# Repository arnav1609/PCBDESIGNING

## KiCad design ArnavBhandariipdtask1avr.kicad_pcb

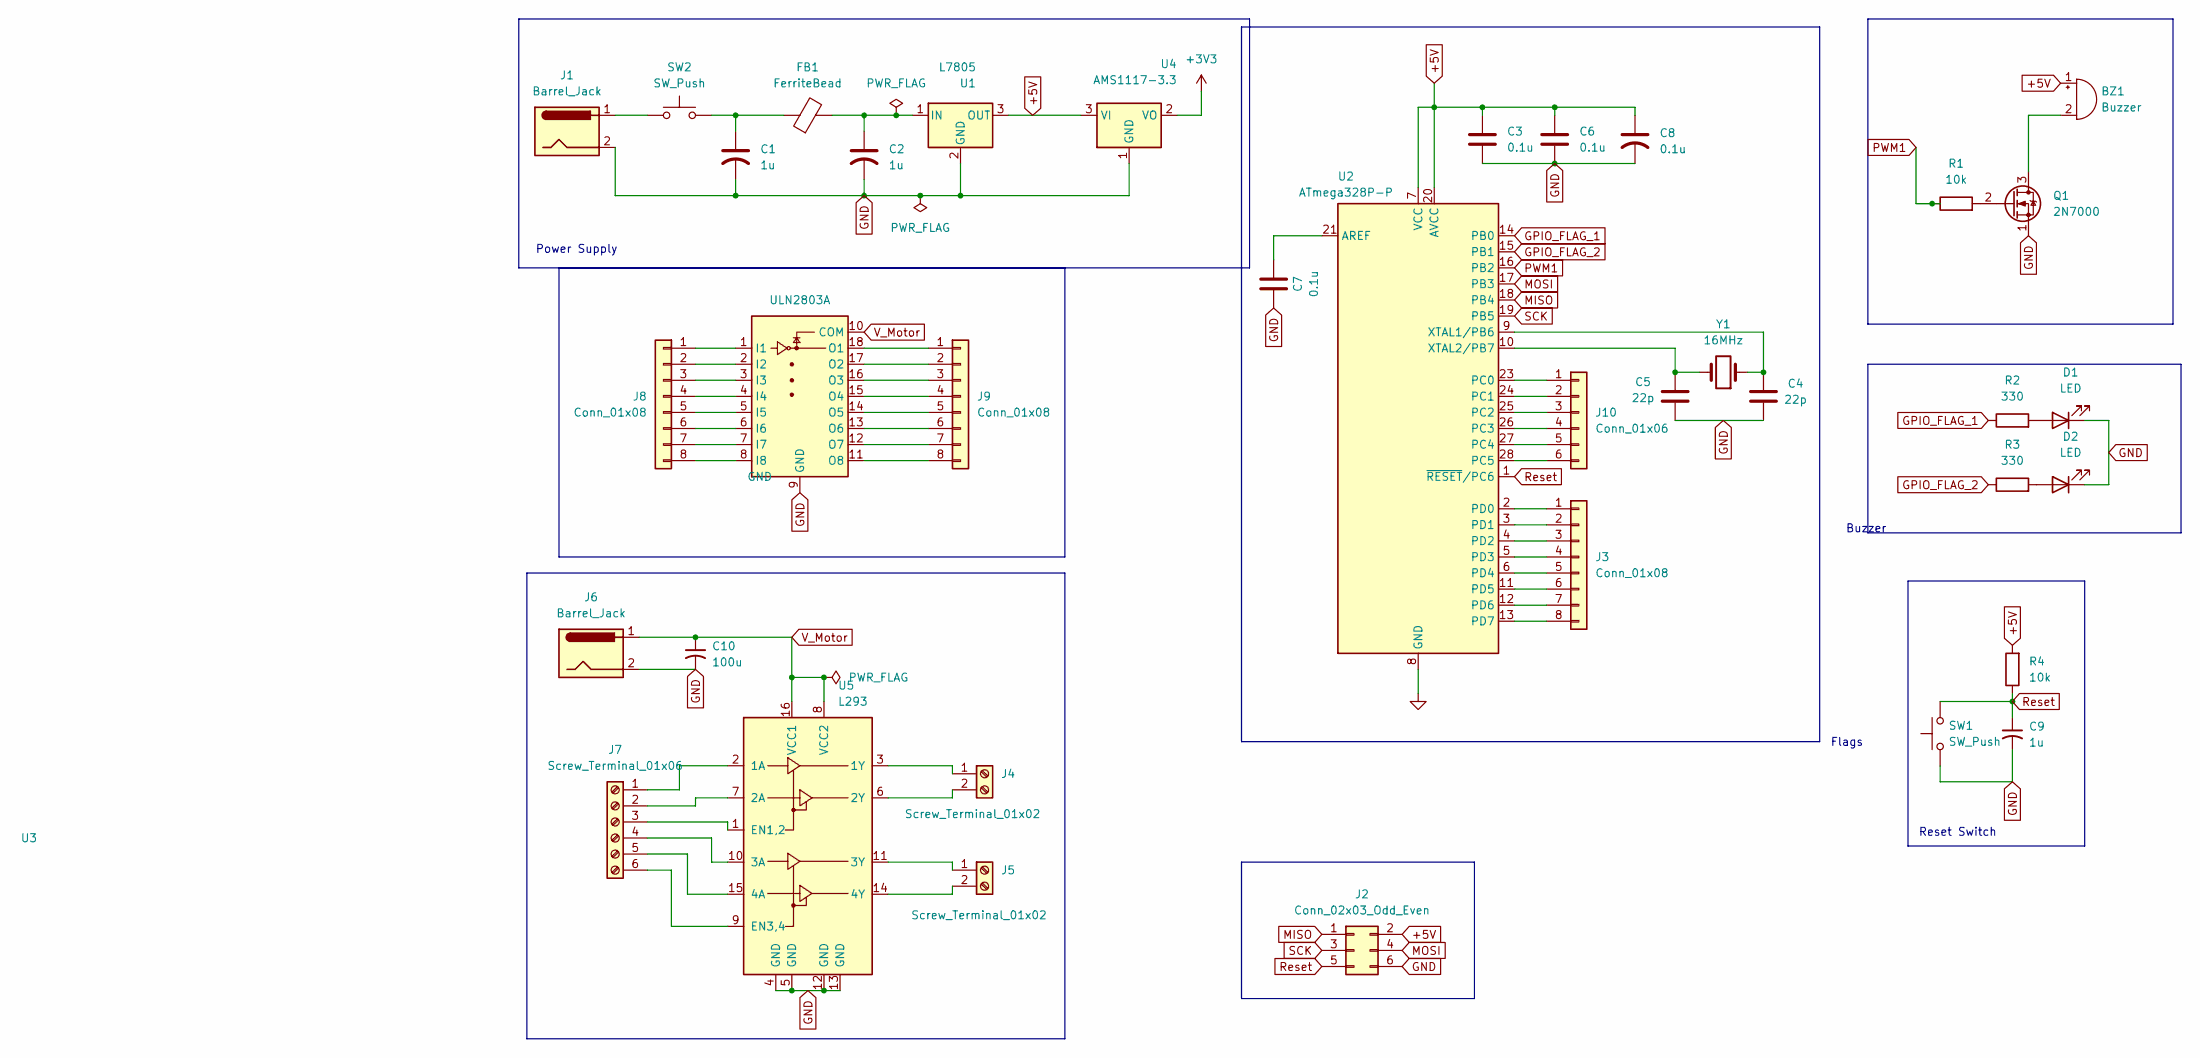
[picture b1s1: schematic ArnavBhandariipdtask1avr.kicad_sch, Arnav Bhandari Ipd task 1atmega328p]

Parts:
BZ1: Buzzer; Buzzer_12x9.5RM7.6
C1, C2, C9: 1u; CP_Radial_D5.0mm_P2.00mm
C3, C6, C7, C8: 0.1u; C_Disc_D3.0mm_W1.6mm_P2.50mm
C4, C5: 22p; C_Disc_D3.0mm_W1.6mm_P2.50mm
C10: 100u; CP_Radial_D6.3mm_P2.50mm
D1, D2: LED; LED_D5.0mm
FB1: FerriteBead; R_Axial_DIN0204_L3.6mm_D1.6mm_P5.08mm_Horizontal
J1, J6: Barrel_Jack; BarrelJack_Horizontal
J2: Conn_02x03_Odd_Even; PinHeader_2x03_P2.54mm_Vertical
J3, J8, J9: Conn_01x08; PinHeader_1x08_P2.54mm_Vertical
J4, J5: Screw_Terminal_01x02; TerminalBlock_Phoenix_PT-1,5-2-3.5-H_1x02_P3.50mm_Horizontal
J7: Screw_Terminal_01x06; TerminalBlock_Phoenix_PT-1,5-6-3.5-H_1x06_P3.50mm_Horizontal
J10: Conn_01x06; PinHeader_1x06_P2.54mm_Vertical
Q1: 2N7000; TO-92_Inline
R1, R4: 10k; R_Axial_DIN0207_L6.3mm_D2.5mm_P7.62mm_Horizontal
R2, R3: 330; R_Axial_DIN0207_L6.3mm_D2.5mm_P7.62mm_Horizontal
SW1, SW2: SW_Push; SW_PUSH_6mm
U1: L7805; TO-220-3_Vertical
U2: ATmega328P-P; DIP-28_W7.62mm
U3: ULN2803A; DIP-18_W7.62mm
U4: AMS1117-3.3; SOT-223-3_TabPin2
U5: L293; DIP-16_W7.62mm
Y1: 16MHz; Crystal_HC49-U_Vertical

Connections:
+3V3: U4.2 (VO)
+5V: BZ1.1 (+), C3.1, C6.1, C8.1, J2.2, R4.2, U1.3 (OUT), U2.7 (VCC), U2.20 (AVCC), U4.3 (VI)
GND: C1.2, C2.2, C3.2, C4.2, C5.1, C6.2, C7.1, C8.2, C9.2, C10.2, D1.1 (K), D2.1 (K), J1.2, J2.6, J6.2, Q1.1 (S), SW1.1, U1.2 (GND), U2.8 (GND), U2.22 (GND), U3.9 (GND), U4.1 (GND), U5.4 (GND), U5.5 (GND), U5.12 (GND), U5.13 (GND)
GPIO_FLAG_1: R2.1, U2.14 (PB0)
GPIO_FLAG_2: R3.1, U2.15 (PB1)
MISO: J2.1, U2.18 (PB4)
MOSI: J2.4, U2.17 (PB3)
unnamed: BZ1.2 (-), Q1.3 (D)
unnamed: C1.1, FB1.1, SW2.2
unnamed: D1.2 (A), R2.2
unnamed: D2.2 (A), R3.2
unnamed: J1.1, SW2.1
unnamed: J3.1, U2.2 (PD0)
unnamed: J3.2, U2.3 (PD1)
unnamed: J3.3, U2.4 (PD2)
unnamed: J3.4, U2.5 (PD3)
unnamed: J3.5, U2.6 (PD4)
unnamed: J3.6, U2.11 (PD5)
unnamed: J3.7, U2.12 (PD6)
unnamed: J3.8, U2.13 (PD7)
unnamed: J4.1, U5.3 (1Y)
unnamed: J4.2, U5.6 (2Y)
unnamed: J5.1, U5.11 (3Y)
unnamed: J5.2, U5.14 (4Y)
unnamed: J7.1, U5.2 (1A)
unnamed: J7.2, U5.7 (2A)
unnamed: J7.3, U5.1 (EN1,2)
unnamed: J7.4, U5.10 (3A)
unnamed: J7.5, U5.15 (4A)
unnamed: J7.6, U5.9 (EN3,4)
unnamed: J8.1, U3.1 (I1)
unnamed: J8.2, U3.2 (I2)
unnamed: J8.3, U3.3 (I3)
unnamed: J8.4, U3.4 (I4)
unnamed: J8.5, U3.5 (I5)
unnamed: J8.6, U3.6 (I6)
unnamed: J8.7, U3.7 (I7)
unnamed: J8.8, U3.8 (I8)
unnamed: J9.1, U3.18 (O1)
unnamed: J9.2, U3.17 (O2)
unnamed: J9.3, U3.16 (O3)
unnamed: J9.4, U3.15 (O4)
unnamed: J9.5, U3.14 (O5)
unnamed: J9.6, U3.13 (O6)
unnamed: J9.7, U3.12 (O7)
unnamed: J9.8, U3.11 (O8)
unnamed: J10.1, U2.23 (PC0)
unnamed: J10.2, U2.24 (PC1)
unnamed: J10.3, U2.25 (PC2)
unnamed: J10.4, U2.26 (PC3)
unnamed: J10.5, U2.27 (PC4)
unnamed: J10.6, U2.28 (PC5)
unnamed: Q1.2 (G), R1.2
unnamed: C2.1, FB1.2, U1.1 (IN)
unnamed: C7.2, U2.21 (AREF)
unnamed: C4.1, U2.9 (XTAL1/PB6), Y1.1
unnamed: C5.2, U2.10 (XTAL2/PB7), Y1.2
PWM1: R1.1, U2.16 (PB2)
Reset: C9.1, J2.5, R4.1, SW1.2, U2.1 (~RESET/PC6)
SCK: J2.3, U2.19 (PB5)
V_Motor: C10.1, J6.1, U3.10 (COM), U5.8 (VCC2), U5.16 (VCC1)

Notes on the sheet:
Flags
Buzzer
Reset Switch
Power Supply

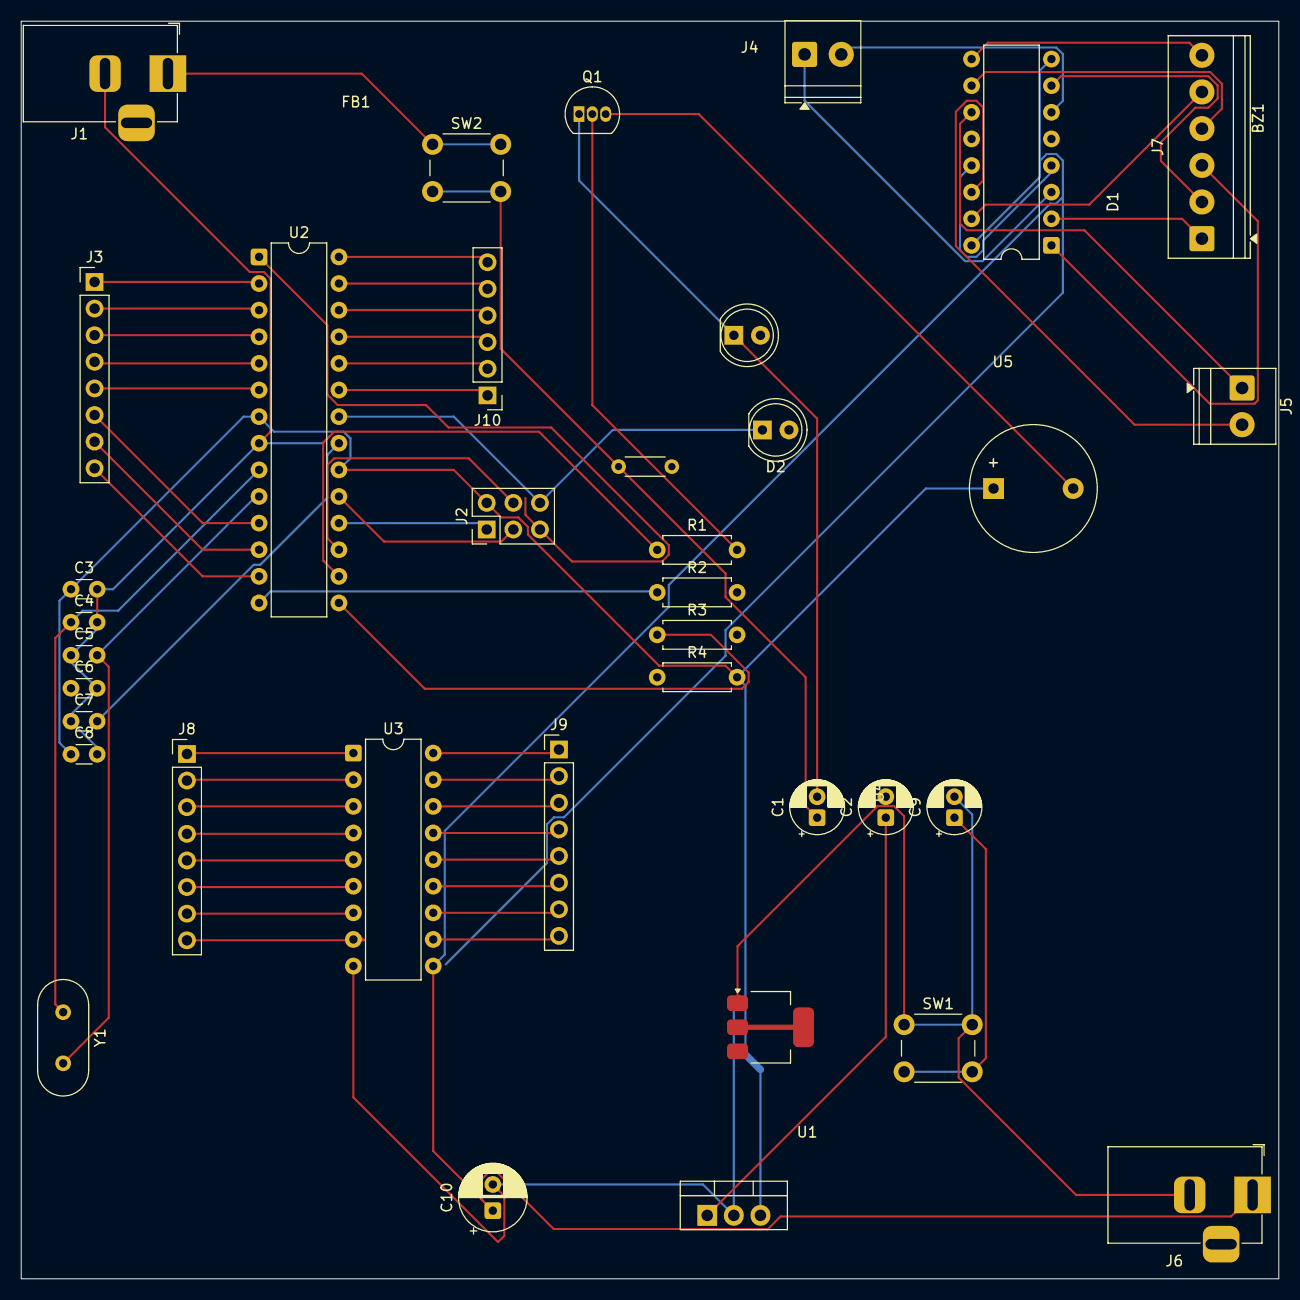
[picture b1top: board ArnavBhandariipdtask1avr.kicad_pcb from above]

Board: 2 copper layers, 120.0 x 120.0 mm, 37 parts (0 on the bottom side), 60 nets.

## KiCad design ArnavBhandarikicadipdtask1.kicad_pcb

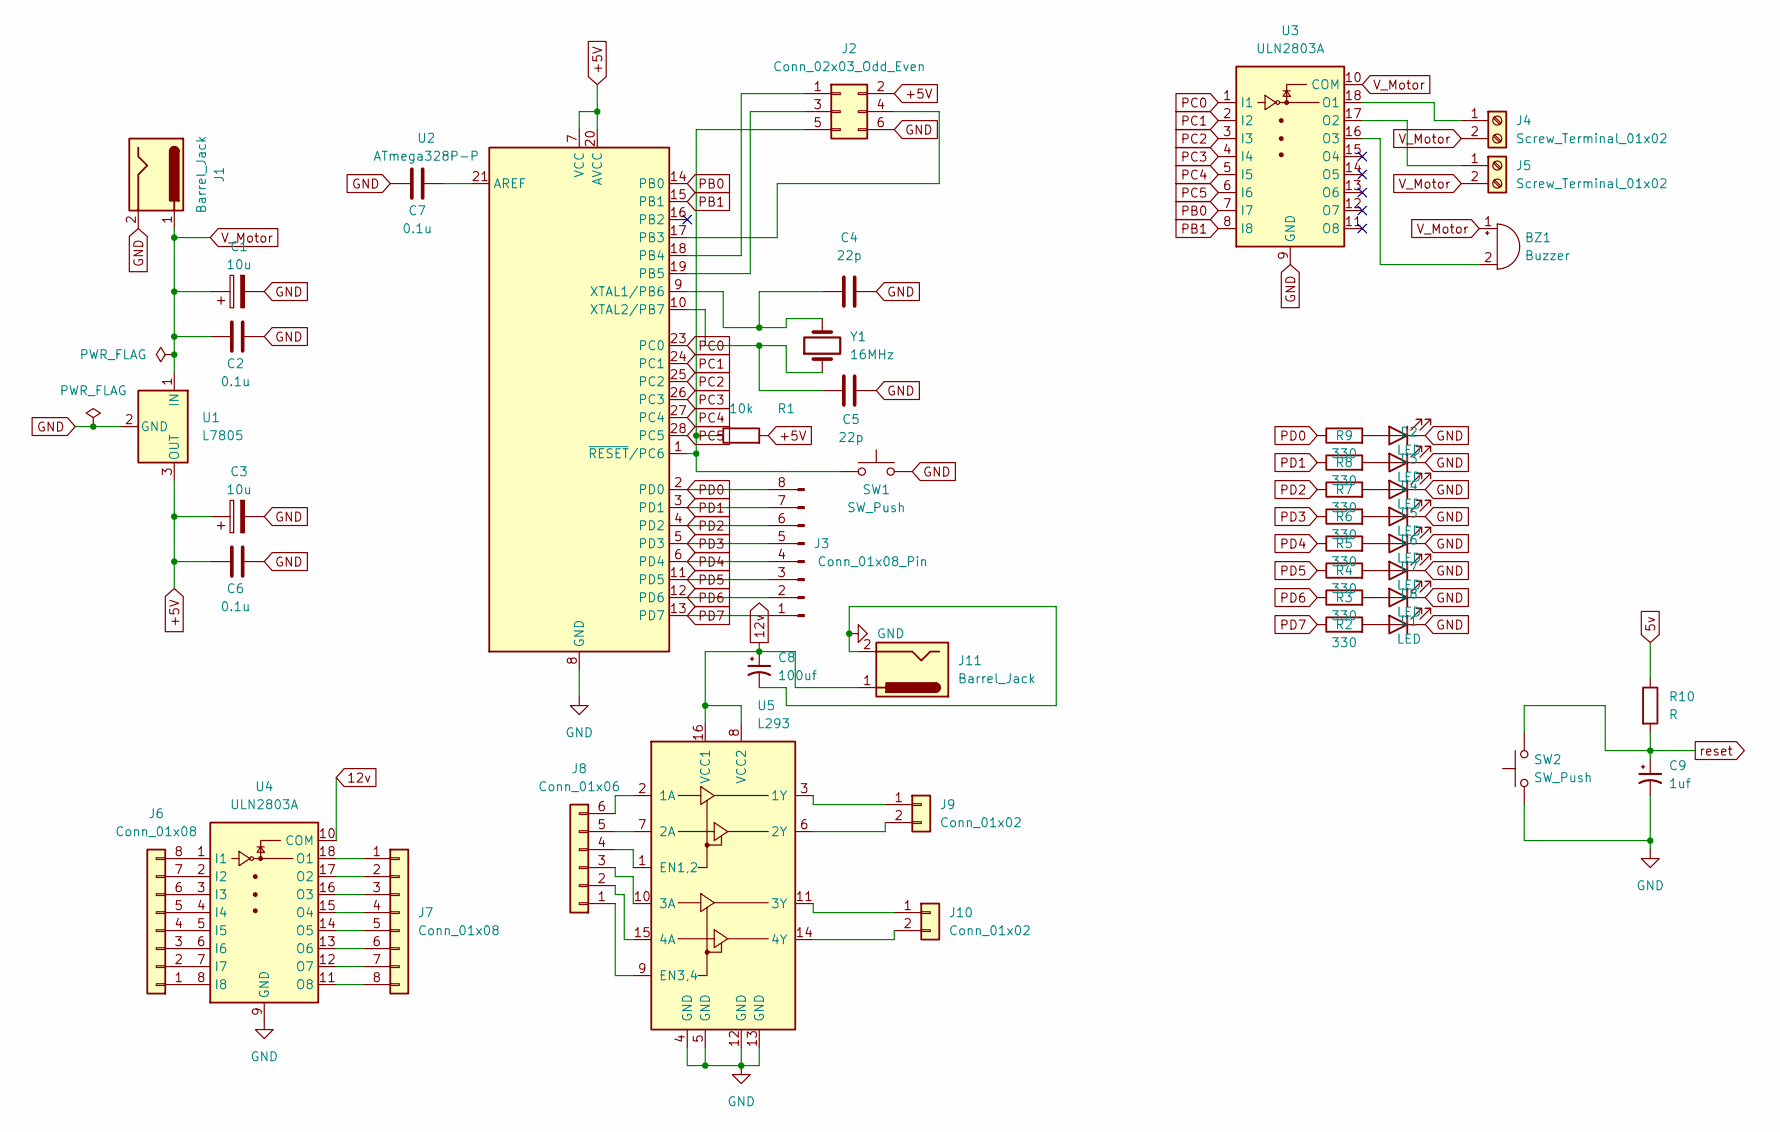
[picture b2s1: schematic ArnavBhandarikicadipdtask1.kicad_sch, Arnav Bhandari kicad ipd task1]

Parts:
BZ1: Buzzer; Buzzer_12x9.5RM7.6
C1, C3: 10u; CP_Radial_D5.0mm_P2.00mm
C2, C6, C7: 0.1u; C_Disc_D3.0mm_W1.6mm_P2.50mm
C4, C5: 22p; C_Disc_D3.0mm_W1.6mm_P2.50mm
C8: 100uf; CP_Radial_D8.0mm_P3.50mm
C9: 1uf; C_Disc_D5.0mm_W2.5mm_P5.00mm
D1, D2, D3, D4, D5, D6, D7, D8: LED; LED_D5.0mm
J1, J11: Barrel_Jack; BarrelJack_Horizontal
J2: Conn_02x03_Odd_Even; PinHeader_2x03_P2.54mm_Vertical
J3: Conn_01x08_Pin; PinHeader_1x08_P2.54mm_Vertical
J4, J5: Screw_Terminal_01x02; TerminalBlock_Phoenix_PT-1,5-2-3.5-H_1x02_P3.50mm_Horizontal
J6, J7: Conn_01x08; PinHeader_1x08_P2.54mm_Vertical
J8: Conn_01x06; PinHeader_1x06_P2.54mm_Vertical
J9, J10: Conn_01x02; PinHeader_1x02_P2.54mm_Vertical
R1: 10k; R_Axial_DIN0207_L6.3mm_D2.5mm_P7.62mm_Horizontal
R2, R3, R4, R5, R6, R7, R8, R9: 330; R_Axial_DIN0207_L6.3mm_D2.5mm_P7.62mm_Horizontal
R10: R; R_Axial_DIN0207_L6.3mm_D2.5mm_P7.62mm_Horizontal
SW1, SW2: SW_Push; SW_PUSH_6mm
U1: L7805; TO-220-3_Vertical
U2: ATmega328P-P; DIP-28_W7.62mm
U3, U4: ULN2803A; DIP-18_W7.62mm
U5: L293; DIP-16_W7.62mm
Y1: 16MHz; Crystal_HC49-U_Vertical

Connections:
5v: R10.1
12v: C8.1, J11.1, U4.10 (COM), U5.8 (VCC2), U5.16 (VCC1)
+5V: C3.1, C6.1, J2.2, R1.2, U1.3 (OUT), U2.7 (VCC), U2.20 (AVCC)
GND: C1.2, C2.2, C3.2, C4.2, C5.1, C6.2, C7.1, C8.2, C9.2, D1.1 (K), D2.1 (K), D3.1 (K), D4.1 (K), D5.1 (K), D6.1 (K), D7.1 (K), D8.1 (K), J1.2, J2.6, J11.2, SW1.2, SW2.1, U1.2 (GND), U2.8 (GND), U2.22 (GND), U3.9 (GND), U4.9 (GND), U5.4 (GND), U5.5 (GND), U5.12 (GND), U5.13 (GND)
unnamed: BZ1.2 (-), U3.16 (O3)
unnamed: D1.2 (A), R2.2
unnamed: D2.2 (A), R9.2
unnamed: D3.2 (A), R8.2
unnamed: D4.2 (A), R7.2
unnamed: D5.2 (A), R6.2
unnamed: D6.2 (A), R5.2
unnamed: D7.2 (A), R4.2
unnamed: D8.2 (A), R3.2
unnamed: J2.1, U2.18 (PB4)
unnamed: J2.3, U2.19 (PB5)
unnamed: J2.4, U2.17 (PB3)
unnamed: J2.5, R1.1, SW1.1, U2.1 (~RESET/PC6)
unnamed: J4.1, U3.18 (O1)
unnamed: J5.1, U3.17 (O2)
unnamed: J6.1, U4.8 (I8)
unnamed: J6.2, U4.7 (I7)
unnamed: J6.3, U4.6 (I6)
unnamed: J6.4, U4.5 (I5)
unnamed: J6.5, U4.4 (I4)
unnamed: J6.6, U4.3 (I3)
unnamed: J6.7, U4.2 (I2)
unnamed: J6.8, U4.1 (I1)
unnamed: J7.1, U4.18 (O1)
unnamed: J7.2, U4.17 (O2)
unnamed: J7.3, U4.16 (O3)
unnamed: J7.4, U4.15 (O4)
unnamed: J7.5, U4.14 (O5)
unnamed: J7.6, U4.13 (O6)
unnamed: J7.7, U4.12 (O7)
unnamed: J7.8, U4.11 (O8)
unnamed: J8.1, U5.9 (EN3,4)
unnamed: J8.2, U5.15 (4A)
unnamed: J8.3, U5.10 (3A)
unnamed: J8.4, U5.1 (EN1,2)
unnamed: J8.5, U5.7 (2A)
unnamed: J8.6, U5.2 (1A)
unnamed: J9.1, U5.3 (1Y)
unnamed: J9.2, U5.6 (2Y)
unnamed: J10.1, U5.11 (3Y)
unnamed: J10.2, U5.14 (4Y)
unnamed: C7.2, U2.21 (AREF)
unnamed: C4.1, U2.9 (XTAL1/PB6), Y1.2
unnamed: C5.2, U2.10 (XTAL2/PB7), Y1.1
PB0: U2.14 (PB0), U3.7 (I7)
PB1: U2.15 (PB1), U3.8 (I8)
PC0: U2.23 (PC0), U3.1 (I1)
PC1: U2.24 (PC1), U3.2 (I2)
PC2: U2.25 (PC2), U3.3 (I3)
PC3: U2.26 (PC3), U3.4 (I4)
PC4: U2.27 (PC4), U3.5 (I5)
PC5: U2.28 (PC5), U3.6 (I6)
PD0: J3.8, R9.1, U2.2 (PD0)
PD1: J3.7, R8.1, U2.3 (PD1)
PD2: J3.6, R7.1, U2.4 (PD2)
PD3: J3.5, R6.1, U2.5 (PD3)
PD4: J3.4, R5.1, U2.6 (PD4)
PD5: J3.3, R4.1, U2.11 (PD5)
PD6: J3.2, R3.1, U2.12 (PD6)
PD7: J3.1, R2.1, U2.13 (PD7)
V_Motor: BZ1.1 (+), C1.1, C2.1, J1.1, J4.2, J5.2, U1.1 (IN), U3.10 (COM)
reset: C9.1, R10.2, SW2.2

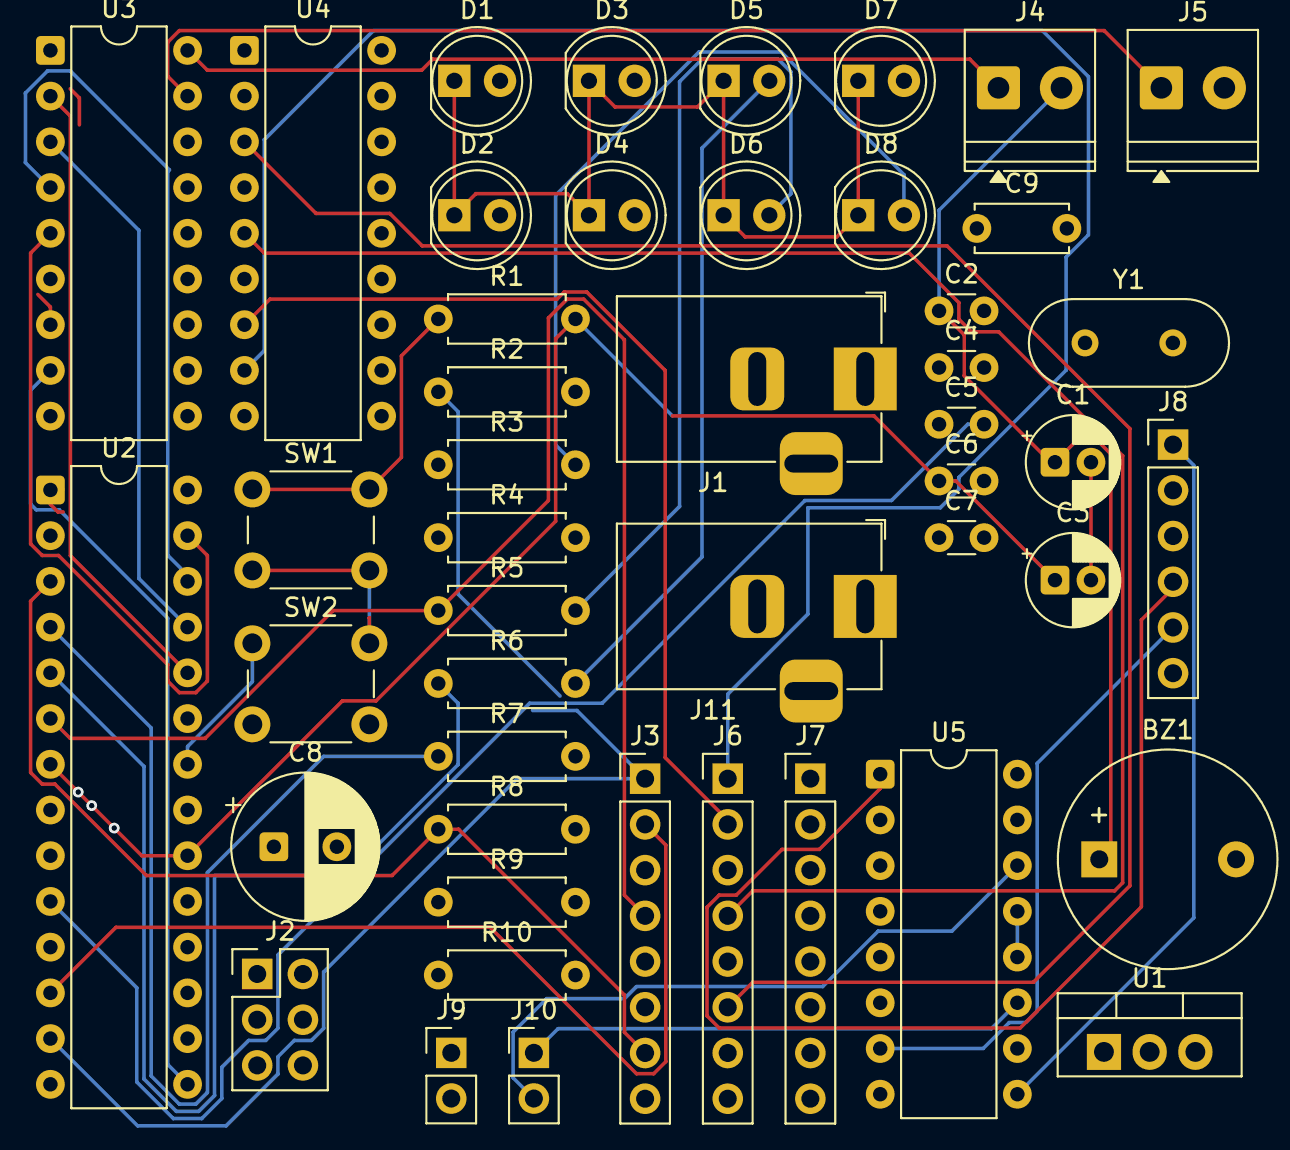
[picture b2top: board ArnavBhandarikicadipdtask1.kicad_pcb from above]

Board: 2 copper layers, 47 parts (0 on the bottom side), 65 nets.

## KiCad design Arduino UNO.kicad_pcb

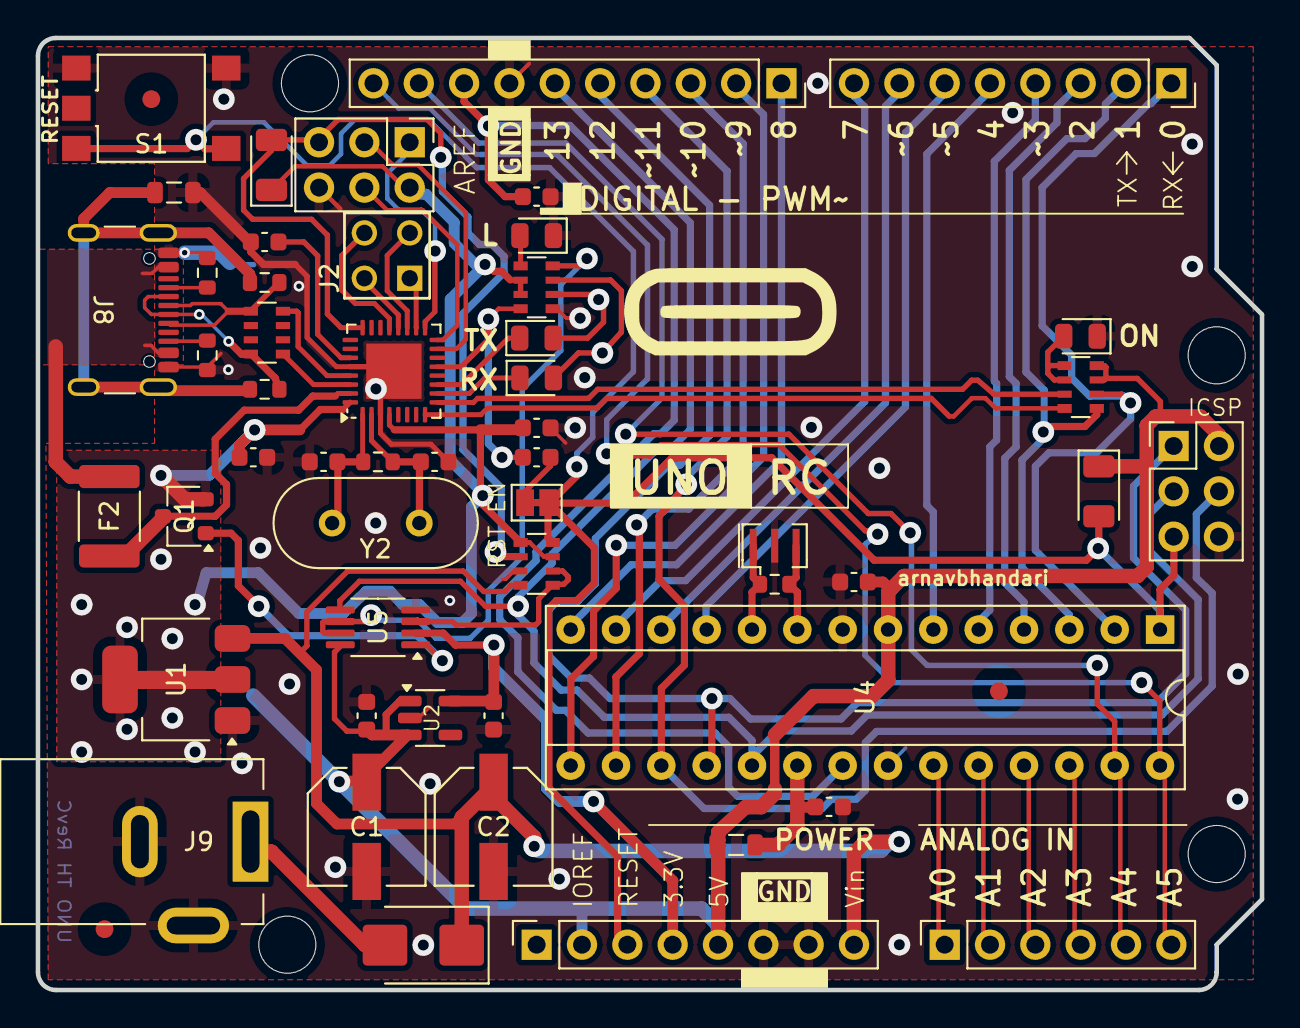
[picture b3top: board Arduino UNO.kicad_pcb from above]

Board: 2 copper layers, 68.6 x 53.3 mm, 56 parts (1 on the bottom side), 62 nets.

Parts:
C1, C2: 47u; CAP_EEHZA1E470P
C3, C4, C6, C7, C8, C9, C12: 100n; C_0603_1608Metric
C5, C10: 1u; C_0603_1608Metric
C11, C13: 22p; C_0603_1608Metric
D1: CGRB307-G; D_SMB
D2, D3: CD1206-S01575; D_1206_3216Metric
D4, D5, D6: YELLOW; LED_0805_2012Metric
D7: GREEN; LED_0805_2012Metric
F2: MF-MSMF050-2; Fuse_1812_4532Metric_Pad1.30x3.40mm_HandSolder
FB1: 1kΩ@100MHz; L_0805_2012Metric
FB2: 10uH; L_0805_2012Metric
FID1, FID2, FID3: Fiducial; Fiducial_1mm_Mask3mm
J1, J3: M20-9980345; PinHeader_2x03_P2.54mm_Vertical
J2: M20-9980245; CONN_M20-9980245_HRW
J4: PPTC101LFBN-RC; PinSocket_1x10_P2.54mm_Vertical
J5, J7: PPTC081LFBN-RC; PinSocket_1x08_P2.54mm_Vertical
J6: PPTC061LFBN-RC; PinSocket_1x06_P2.54mm_Vertical
J8: USB_C_Receptacle_USB2.0_16P; USB_C_Receptacle_GCT_USB4105-xx-A_16P_TopMnt_Horizontal
J9: PJ-102AH; BarrelJack_Kycon_KLDX-0202-xC_Horizontal
JP1, JP2: SolderJumper_2_Open; SolderJumper-2_P1.3mm_Open_Pad1.0x1.5mm
Q1: FDN340P; SC-59
R1, R2: 1M; R_0603_1608Metric
R3, R4: 5k1; R_0603_1608Metric
RN1: 10k; R_Array_Convex_4x0603
RN2, RN4: 1k; R_Array_Convex_4x0603
RN3: 22R; R_Array_Convex_4x0603
S1: TS06-667-30-BK-100-G-SMT-TR; SW_TS06-667-30-BK-100-G-SMT-TR
U1: NCP1117-5.0_SOT223; SOT-223-3_TabPin2
U2: LP2985-3.3; SOT-23-5
U3: ATMEGA16U2-MU; VQFN-32-1EP_5x5mm_P0.5mm_EP3.1x3.1mm
U4: ATMEGA328P-PU; DIP-28_W7.62mm_Socket
U5: LMV358IDGKR; MSOP-8_3x3mm_P0.65mm
Y1: CSTNE16M0V530000R0; Resonator_SMD_Murata_CSTxExxV-3Pin_3.0x1.1mm
Y2: LFXTAL003240BULK; Crystal_HC49-4H_Vertical
Z1, Z2: 5pF@1MHz; R_0603_1608Metric

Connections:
+3.3V: C5.2, J7.4, U2.5 (VOUT), U5.2
+5V: C1.1, C3.2, C4.1, C8.2, C9.1, D2.1 (K), D3.1 (K), FB2.1, J1.2, J3.2, J7.2, J7.5, Q1.2 (S), RN1.3 (R3.1), RN1.5 (R4.2), RN2.2 (R2.1), RN2.3 (R3.1), RN4.3 (R3.1), RN4.4 (R4.1), U1.2 (VO), U2.1 (VIN), U2.3 (ON/~OFF), U3.4 (VCC), U3.32 (AVCC), U4.7 (VCC), U5.8 (VCC+)
AD0: J6.1, U4.23 (PC0)
AD1: J6.2, U4.24 (PC1)
AD2: J6.3, U4.25 (PC2)
AD3: J6.4, U4.26 (PC3)
AD4/SDA: J4.9, J6.5, U4.27 (PC4)
AD5/SCL: J4.10, J6.6, U4.28 (PC5)
AREF: C6.1, J4.8, U4.21 (AREF)
AVCC: C12.1, FB2.2, U4.20 (AVCC)
CC1: J8.A5 (CC1), R3.1
CC2: J8.B5 (CC2), R4.1
CMP: RN1.1 (R1.1), RN1.2 (R2.1), U5.3
D+: J8.A6 (D+), J8.B6 (D+), RN3.5 (R4.2), Z1.1
D-: J8.A7 (D-), J8.B7 (D-), RN3.8 (R1.2), Z2.1
DTR: C7.1, RN2.4 (R4.1), U3.13 (PD7)
GATE_CMD: Q1.1 (G), U5.1
GND: C1.2, C2.2, C3.1, C4.2, C5.1, C6.2, C8.1, C9.2, C10.1, C11.2, C12.2, C13.2, D4.1 (K), D7.1 (K), FB1.2, J1.6, J3.6, J4.7, J7.6, J7.7, J8.A1 (GND), J8.A12 (GND), J8.B1 (GND), J8.B12 (GND), J9.2, J9.3, JP2.1 (A), JP2.2 (B), R3.2, R4.2, RN1.7 (R2.2), RN2.5 (R4.2), S1.1, S1.2, U1.1 (GND), U2.2 (GND), U3.3 (GND), U3.28 (UGND), U3.33 (EXP), U4.8 (GND), U4.22 (GND__1), U5.4 (GND), Y1.2
IO0: J5.1, RN4.2 (R2.1), U4.2 (PD0)
IO1: J5.2, RN4.1 (R1.1), U4.3 (PD1)
IO2: J5.3, U4.4 (PD2)
IO3: J5.4, U4.5 (PD3)
IO4: J5.5, U4.6 (PD4)
IO5: J5.6, U4.11 (PD5)
IO6: J5.7, U4.12 (PD6)
IO7: J5.8, U4.13 (PD7)
IO8: J4.1, U4.14 (PB0)
IO9: J4.2, U4.15 (PB1)
M8RXD: RN4.7 (R2.2), U3.9 (PD3)
M8TXD: RN4.8 (R1.2), U3.8 (PD2)
MISO: J3.1, J4.5, U4.18 (PB4)
MISO2: J1.1, U3.17 (PB3)
MOSI: J3.4, J4.4, U4.17 (PB3)
MOSI2: J1.4, U3.16 (PB2)
unnamed: D1.2 (A), J9.1
unnamed: D4.2 (A), RN2.1 (R1.1)
unnamed: D5.2 (A), RN2.6 (R3.2)
unnamed: D6.2 (A), RN2.7 (R2.2)
unnamed: D7.2 (A), RN4.5 (R4.2), RN4.6 (R3.2)
unnamed: RN2.8 (R1.2), U5.6, U5.7
unnamed: C13.1, R1.1, U3.2 (PC0), Y2.1
unnamed: C10.2, U3.27 (UCAP)
unnamed: C11.1, R1.2, U3.1 (XTAL1), Y2.2
unnamed: R2.2, U4.9 (PB6), Y1.3
unnamed: R2.1, U4.10 (PB7), Y1.1
PB4: J2.1, U3.18 (PB4)
PB5: J2.3, U3.19 (PB5)
PB6: J2.2, U3.20 (PB6)
PB7: J2.4, U3.21 (PB7)
RD+: RN3.4 (R4.1), U3.29 (D+)
RD-: RN3.1 (R1.1), U3.30 (D-)
RESET: C7.2, D2.2 (A), J3.5, J7.3, JP1.1 (A), JP1.2 (B), RN1.4 (R4.1), S1.3, S1.4, U4.1 (PC6/~RESET)
RESET2: D3.2 (A), J1.5, RN1.6 (R3.2), U3.24 (PC1//~RESET)
RXLED: D6.1 (K), U3.10 (PD4)
SCK: J3.3, J4.6, U4.19 (PB5), U5.5
SCK2: J1.3, U3.15 (PB1)
SS: J4.3, U4.16 (PB2)
TXLED: D5.1 (K), U3.11 (PD5)
USBVCC: F2.2, Q1.3 (D), U3.31 (UVCC)
USHIELD: FB1.1, J8.S1 (SHIELD), Z1.2, Z2.2
VCC: C2.1, D1.1 (K), J7.8, RN1.8 (R1.2), U1.3 (VI)
XUSB: F2.1, J8.A4 (VBUS), J8.A9 (VBUS), J8.B4 (VBUS), J8.B9 (VBUS)
